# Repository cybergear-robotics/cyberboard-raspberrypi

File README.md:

# CyberBoard - Raspberry PI 4

This is the Kicad project for the CyberBoard Raspberry PI HAT. It has an ESP32S3 which is
connected via UART to the Raspberry PI. The microcontroller drives the cybergear 
motors via CAN. Furthermore a MOLEX CLIK connector is integrated in order
to communicate with the power distribution board [Holybro PM03D Pixhawk 5X Power
Module](https://docs.holybro.com/power-module-and-pdb/power-module/digital-power-module-pm-setup).

## Features

* 5V power supply connectior compatible with **Holybro PM03D Pixhawk** with
  support for the INA226 power monitor unit.
* ESP32S3 with dual-core CPU.
* CAN transceiver TJA1051T for communication with **Xiaomi CyberGears**.
* 5V fan connector for Raspberry PI with support for `gpio-fan` (PWM).
* Connector for external WS2812B LEDs.
* Connector 4x GPIO including 3.3V and 5V supply.
* Conenctor for lidar sensors from Slamtec (tested with RPLIDAR A3).
* 2x UART communication lines between ESP32S3 and Raspberry PI.
  * Serial log for debugging purposes, flashing and burning fuse-bits.
  * **ROS2 Serial Agent** communication
* **JTAG** connection between ESP32S3 and Raspberry PI
* Connector for external switch/button with LED support.

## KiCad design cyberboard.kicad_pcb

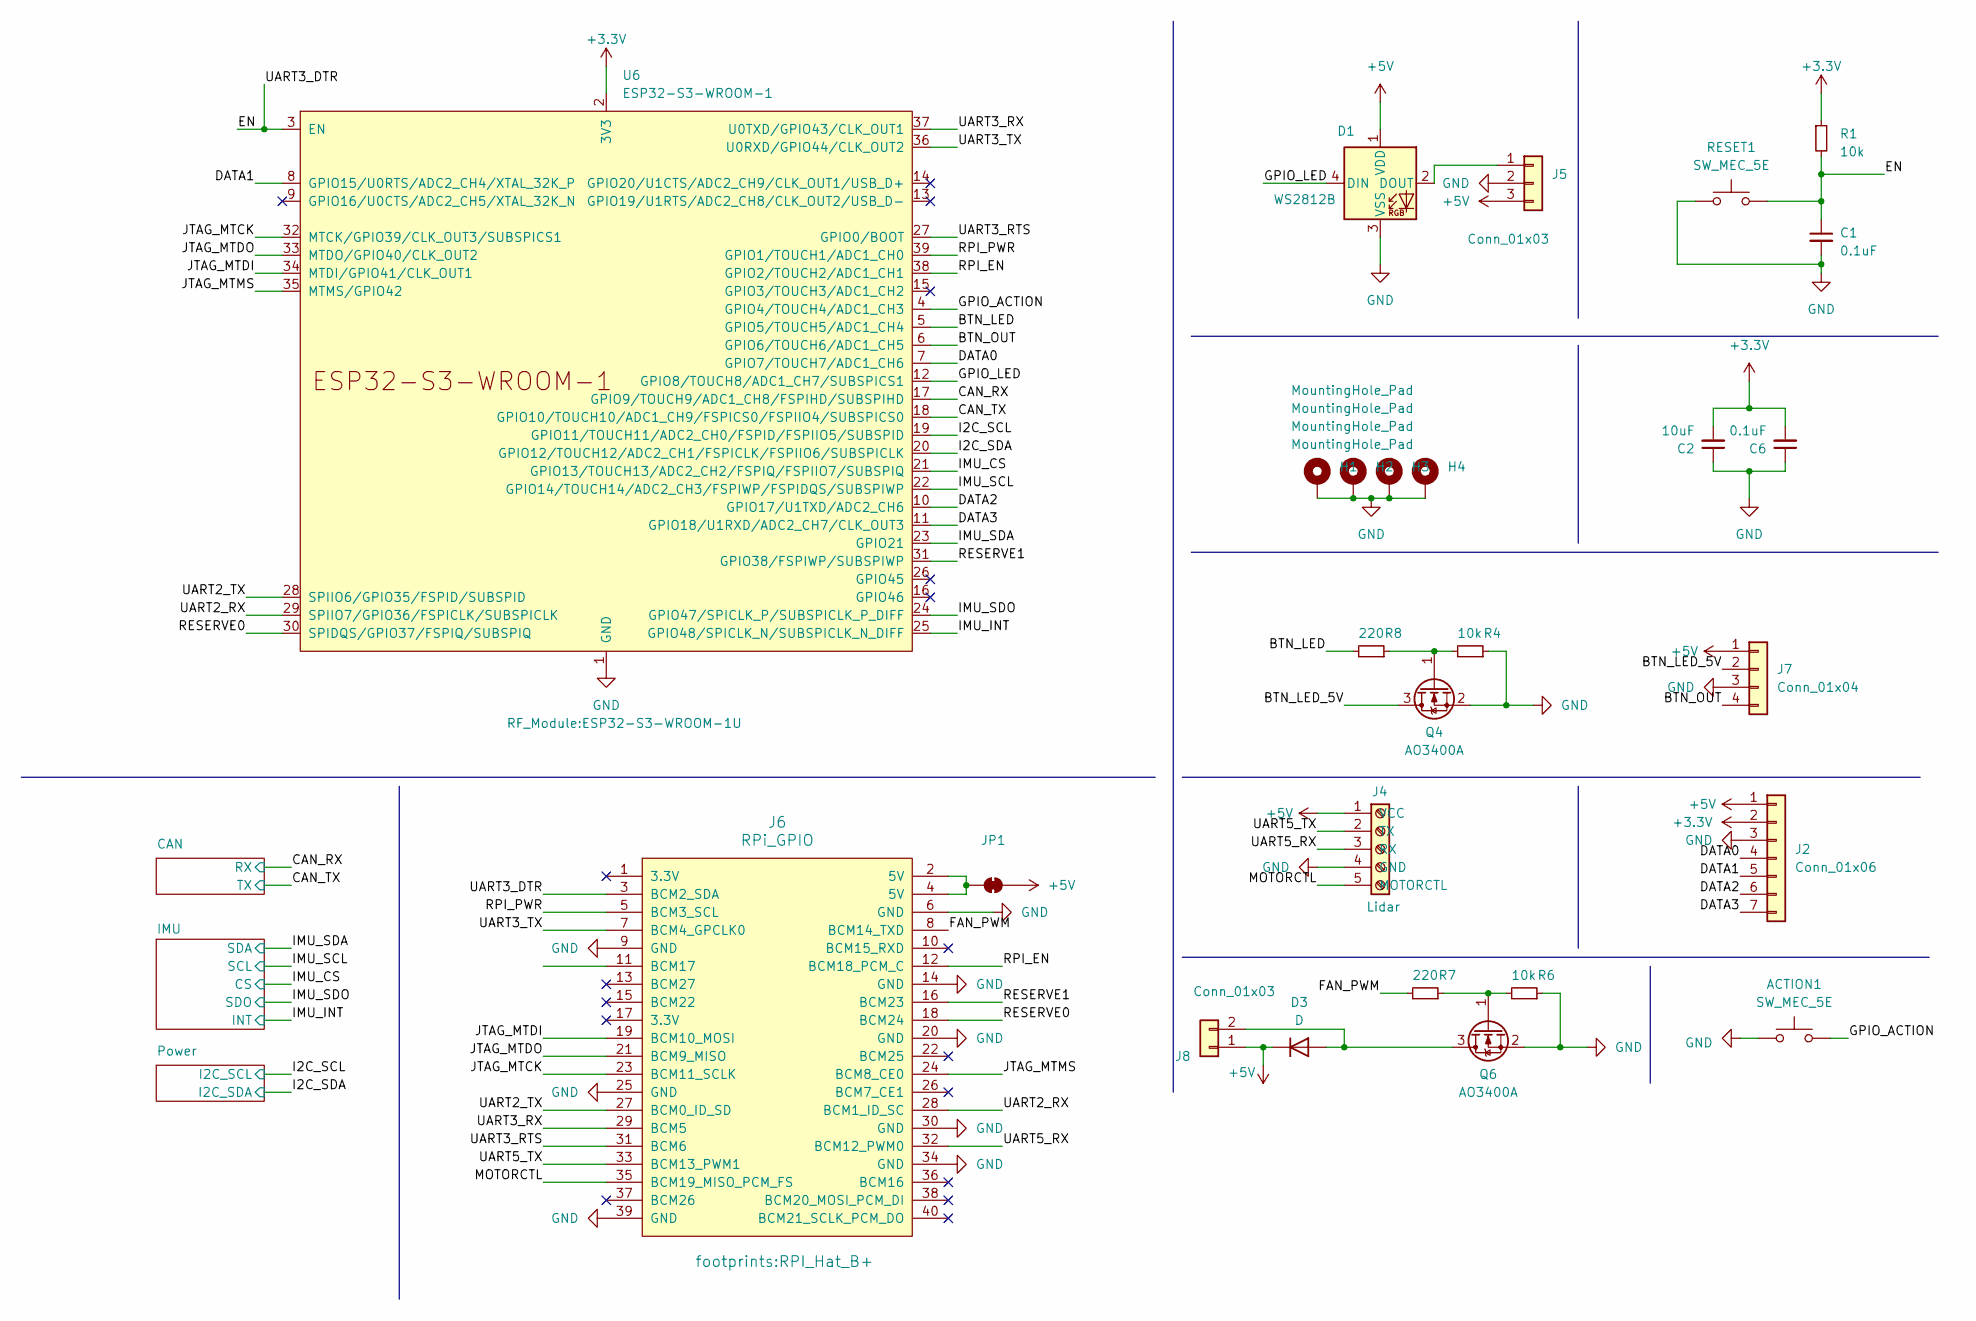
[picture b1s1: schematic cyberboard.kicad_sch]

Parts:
ACTION1: SW_MEC_5E; SW_PUSH_6mm_H5mm; LCSC C318884
C1, C6: 0.1uF; C_0805_2012Metric; LCSC C49678
C2: 10uF; C_0805_2012Metric; LCSC C15850
D1: WS2812B; LED_WS2812B_PLCC4_5.0x5.0mm_P3.2mm
D3: D; D_SOD-323; LCSC C191023
H1, H2, H3, H4: MountingHole_Pad; MountingHole_3.2mm_M3_DIN965_Pad
J2: Conn_01x06; JST_XH_B7B-XH-A_1x07_P2.50mm_Vertical
J4: Lidar; JST_XH_B5B-XH-A_1x05_P2.50mm_Vertical
J5: Conn_01x03; JST_XH_B3B-XH-A_1x03_P2.50mm_Vertical
J6: RPi_GPIO; RPI_Hat_B+
J7: Conn_01x04; JST_XH_B4B-XH-A_1x04_P2.50mm_Vertical
J8: Conn_01x03; JST_XH_B2B-XH-A_1x02_P2.50mm_Vertical
JP1: SolderJumper_2_Open; SolderJumper-2_P1.3mm_Bridged2Bar_RoundedPad1.0x1.5mm
Q4, Q6: AO3400A; SOT-23; LCSC C20917
R1, R4, R6: 10k; R_0805_2012Metric; LCSC C17414
R7, R8: 220; R_0805_2012Metric; LCSC C17557
RESET1: SW_MEC_5E; SW_PUSH_6mm_H5mm; LCSC C318884
U6: ESP32-S3-WROOM-1; ESP32-S3-WROOM-1U

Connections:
+3.3V: C2.2, C6.2, J2.2, R1.1, U6.2 (3V3); also elsewhere on the board
+5V: D1.1 (VDD), D3.1 (K), J2.1, J4.1 (VCC), J5.3, J7.1, J8.1, JP1.2 (B); also elsewhere on the board
/BTN_LED: R8.2, U6.5 (GPIO5/TOUCH5/ADC1_CH4)
/BTN_LED_5V: J7.2, Q4.3 (D)
/BTN_OUT: J7.4, U6.6 (GPIO6/TOUCH6/ADC1_CH5)
/CAN_RX: U6.17 (GPIO9/TOUCH9/ADC1_CH8/FSPIHD/SUBSPIHD); also elsewhere on the board
/CAN_TX: U6.18 (GPIO10/TOUCH10/ADC1_CH9/FSPICS0/FSPIIO4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); also elsewhere on the board
/DATA0: J2.4, U6.7 (GPIO7/TOUCH7/ADC1_CH6)
/DATA1: J2.5, U6.8 (GPIO15/U0RTS/ADC2_CH4/XTAL_32K_P)
/DATA2: J2.6, U6.10 (GPIO17/U1TXD/ADC2_CH6)
/DATA3: J2.7, U6.11 (GPIO18/U1RXD/ADC2_CH7/CLK_OUT3)
/EN: C1.1, J6.3 (BCM2_SDA), R1.2, RESET1.2, U6.3 (EN)
/FAN_PWM: J6.8 (BCM14_TXD), R7.2
/GPIO_ACTION: ACTION1.2, U6.4 (GPIO4/TOUCH4/ADC1_CH3)
/GPIO_LED: D1.4 (DIN), U6.12 (GPIO8/TOUCH8/ADC1_CH7/SUBSPICS1)
/I2C_SCL: U6.19 (GPIO11/TOUCH11/ADC2_CH0/FSPID/FSPIIO5/S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); also elsewhere on the board
/I2C_SDA: U6.20 (GPIO12/TOUCH12/ADC2_CH1/FSPICLK/FSPIIO6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); also elsewhere on the board
/IMU_CS: U6.21 (GPIO13/TOUCH13/ADC2_CH2/FSPIQ/FSPIIO7/S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); also elsewhere on the board
/IMU_INT: U6.25 (GPIO48/SPICLK_N/SUBSPICLK_N_DIFF); also elsewhere on the board
/IMU_SCL: U6.22 (GPIO14/TOUCH14/ADC2_CH3/FSPIWP/FSPIDQS/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); also elsewhere on the board
/IMU_SDA: U6.23 (GPIO21); also elsewhere on the board
/IMU_SDO: U6.24 (GPIO47/SPICLK_P/SUBSPICLK_P_DIFF); also elsewhere on the board
/JTAG_MTCK: J6.23 (BCM11_SCLK), U6.32 (MTCK/GPIO39/CLK_OUT3/SUBSPICS1)
/JTAG_MTDI: J6.19 (BCM10_MOSI), U6.34 (MTDI/GPIO41/CLK_OUT1)
/JTAG_MTDO: J6.21 (BCM9_MISO), U6.33 (MTDO/GPIO40/CLK_OUT2)
/JTAG_MTMS: J6.24 (BCM8_CE0), U6.35 (MTMS/GPIO42)
/MOTORCTL: J4.5 (MOTORCTL), J6.35 (BCM19_MISO_PCM_FS)
/RESERVE0: J6.18 (BCM24), U6.30 (SPIDQS/GPIO37/FSPIQ/SUBSPIQ)
/RESERVE1: J6.16 (BCM23), U6.31 (GPIO38/FSPIWP/SUBSPIWP)
/RPI_EN: J6.12 (BCM18_PCM_C), U6.38 (GPIO2/TOUCH2/ADC1_CH1)
/RPI_PWR: J6.5 (BCM3_SCL), U6.39 (GPIO1/TOUCH1/ADC1_CH0)
/UART2_RX: J6.28 (BCM1_ID_SC), U6.29 (SPIIO7/GPIO36/FSPICLK/SUBSPICLK)
/UART2_TX: J6.27 (BCM0_ID_SD), U6.28 (SPIIO6/GPIO35/FSPID/SUBSPID)
/UART3_RTS: J6.31 (BCM6), U6.27 (GPIO0/BOOT)
/UART3_RX: J6.29 (BCM5), U6.37 (U0TXD/GPIO43/CLK_OUT1)
/UART3_TX: J6.7 (BCM4_GPCLK0), U6.36 (U0RXD/GPIO44/CLK_OUT2)
/UART5_RX: J4.3 (RX), J6.32 (BCM12_PWM0)
/UART5_TX: J4.2 (TX), J6.33 (BCM13_PWM1)
GND: ACTION1.1, C1.2, C2.1, C6.1, D1.3 (VSS), H1.1, H2.1, H3.1, H4.1, J2.3, J4.4 (GND), J5.2, J6.6 (GND), J6.9 (GND), J6.14 (GND), J6.20 (GND), J6.25 (GND), J6.30 (GND), J6.34 (GND), J6.39 (GND), J7.3, Q4.2 (S), Q6.2 (S), R4.1, R6.1, RESET1.1, U6.1 (GND), U6.40 (GND), U6.41 (GND); also elsewhere on the board
unnamed: D1.2 (DOUT), J5.1
unnamed: D3.2 (A), J8.2, Q6.3 (D)
unnamed: J6.2 (5V), J6.4 (5V), JP1.1 (A)
unnamed: Q4.1 (G), R4.2, R8.1
unnamed: Q6.1 (G), R6.2, R7.1

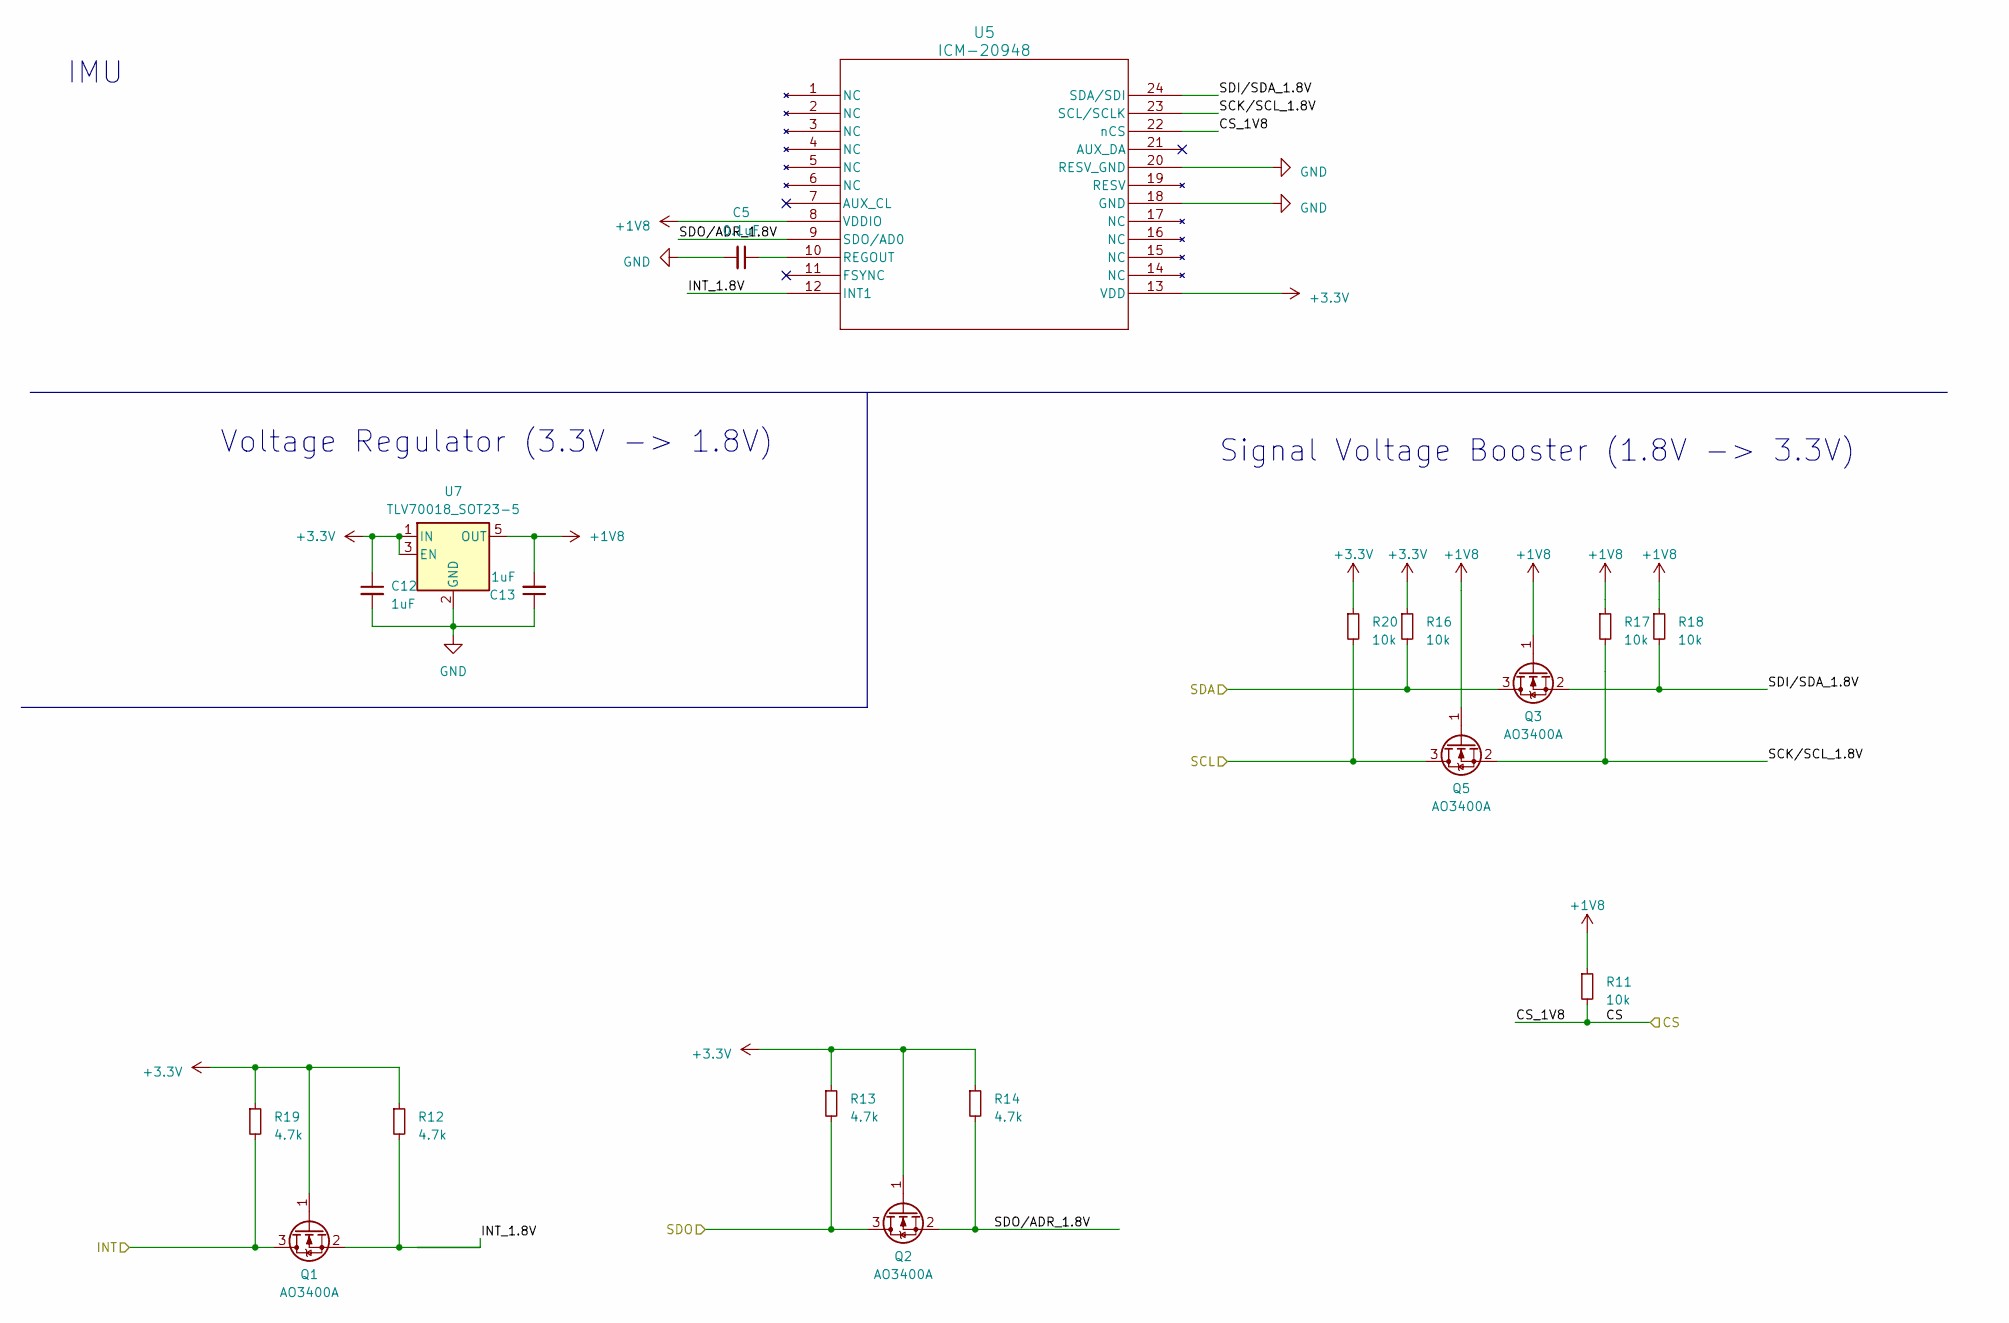
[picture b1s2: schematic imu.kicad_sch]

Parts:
C5: 0.1uF; C_0805_2012Metric; LCSC C49678
C12, C13: 1uF; C_0805_2012Metric; LCSC C28323
Q1, Q2, Q3, Q5: AO3400A; SOT-23; LCSC C20917
R11, R16, R17, R18, R20: 10k; R_0805_2012Metric; LCSC C17414
R12, R13, R14, R19: 4.7k; R_0805_2012Metric; LCSC C17673
U5: ICM-20948; QFN24_3X3X0P9_IVS; LCSC C726001
U7: TLV70018_SOT23-5; SOT-23-5; LCSC C79924

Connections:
+1V8: C13.2, Q3.1 (G), Q5.1 (G), R11.1, R17.1, R18.1, U5.8 (VDDIO), U7.5 (OUT)
+3.3V: C12.1, Q1.1 (G), Q2.1 (G), R12.1, R13.1, R14.1, R16.1, R19.1, R20.1, U5.13 (VDD), U7.1 (IN), U7.3 (EN); also elsewhere on the board
/IMU/INT_1.8V: Q1.2 (S), R12.2, U5.12 (INT1)
/IMU_CS: R11.2, U5.22 (nCS); also elsewhere on the board
/IMU_INT: Q1.3 (D), R19.2; also elsewhere on the board
/IMU_SCL: Q5.3 (D), R20.2; also elsewhere on the board
/IMU_SDA: Q3.3 (D), R16.2; also elsewhere on the board
/IMU_SDO: Q2.3 (D), R13.2; also elsewhere on the board
GND: C5.2, C12.2, C13.1, U5.18 (GND), U5.20 (RESV_GND), U7.2 (GND); also elsewhere on the board
unnamed: C5.1, U5.10 (REGOUT)

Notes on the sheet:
IMU
Signal Voltage Booster (1.8V -> 3.3V)
Voltage Regulator (3.3V -> 1.8V)

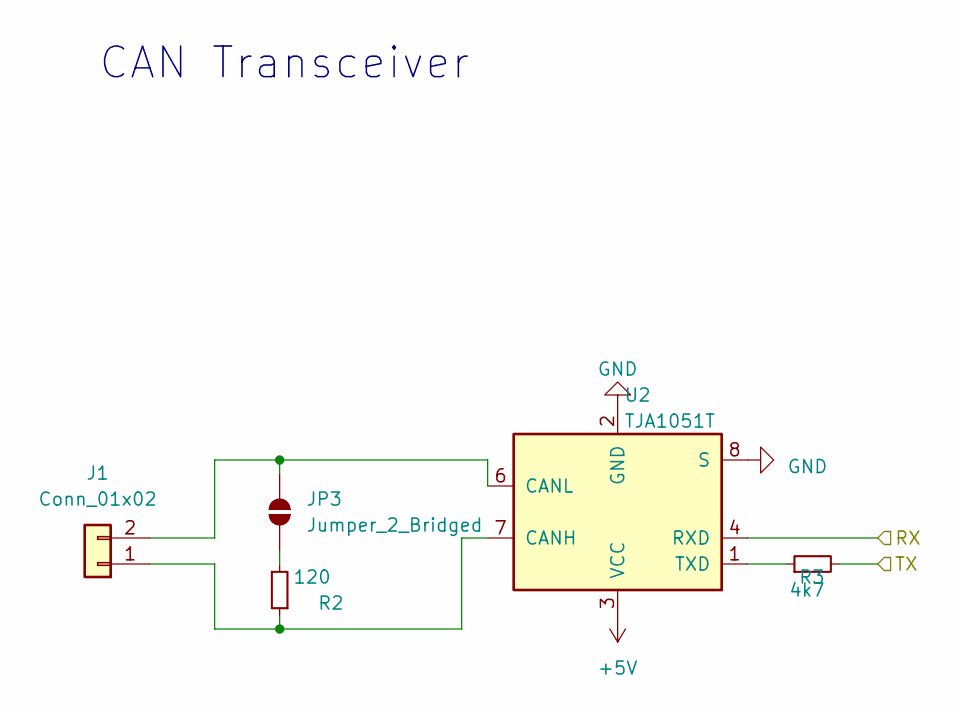
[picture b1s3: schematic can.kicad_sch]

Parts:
J1: Conn_01x02; JST_XH_B2B-XH-A_1x02_P2.50mm_Vertical
JP3: Jumper_2_Bridged; SolderJumper-2_P1.3mm_Open_RoundedPad1.0x1.5mm
R2: 120; R_0805_2012Metric; LCSC C17437
R3: 4k7; R_0805_2012Metric; LCSC C17673
U2: TJA1051T; SOIC-8_3.9x4.9mm_P1.27mm; LCSC C92211

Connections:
+5V: U2.3 (VCC); also elsewhere on the board
/CAN_RX: U2.4 (RXD); also elsewhere on the board
/CAN_TX: R3.2; also elsewhere on the board
GND: U2.2 (GND), U2.8 (S); also elsewhere on the board
unnamed: J1.1, R2.1, U2.7 (CANH)
unnamed: J1.2, JP3.2 (B), U2.6 (CANL)
unnamed: JP3.1 (A), R2.2
unnamed: R3.1, U2.1 (TXD)

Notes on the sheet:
CAN Transceiver

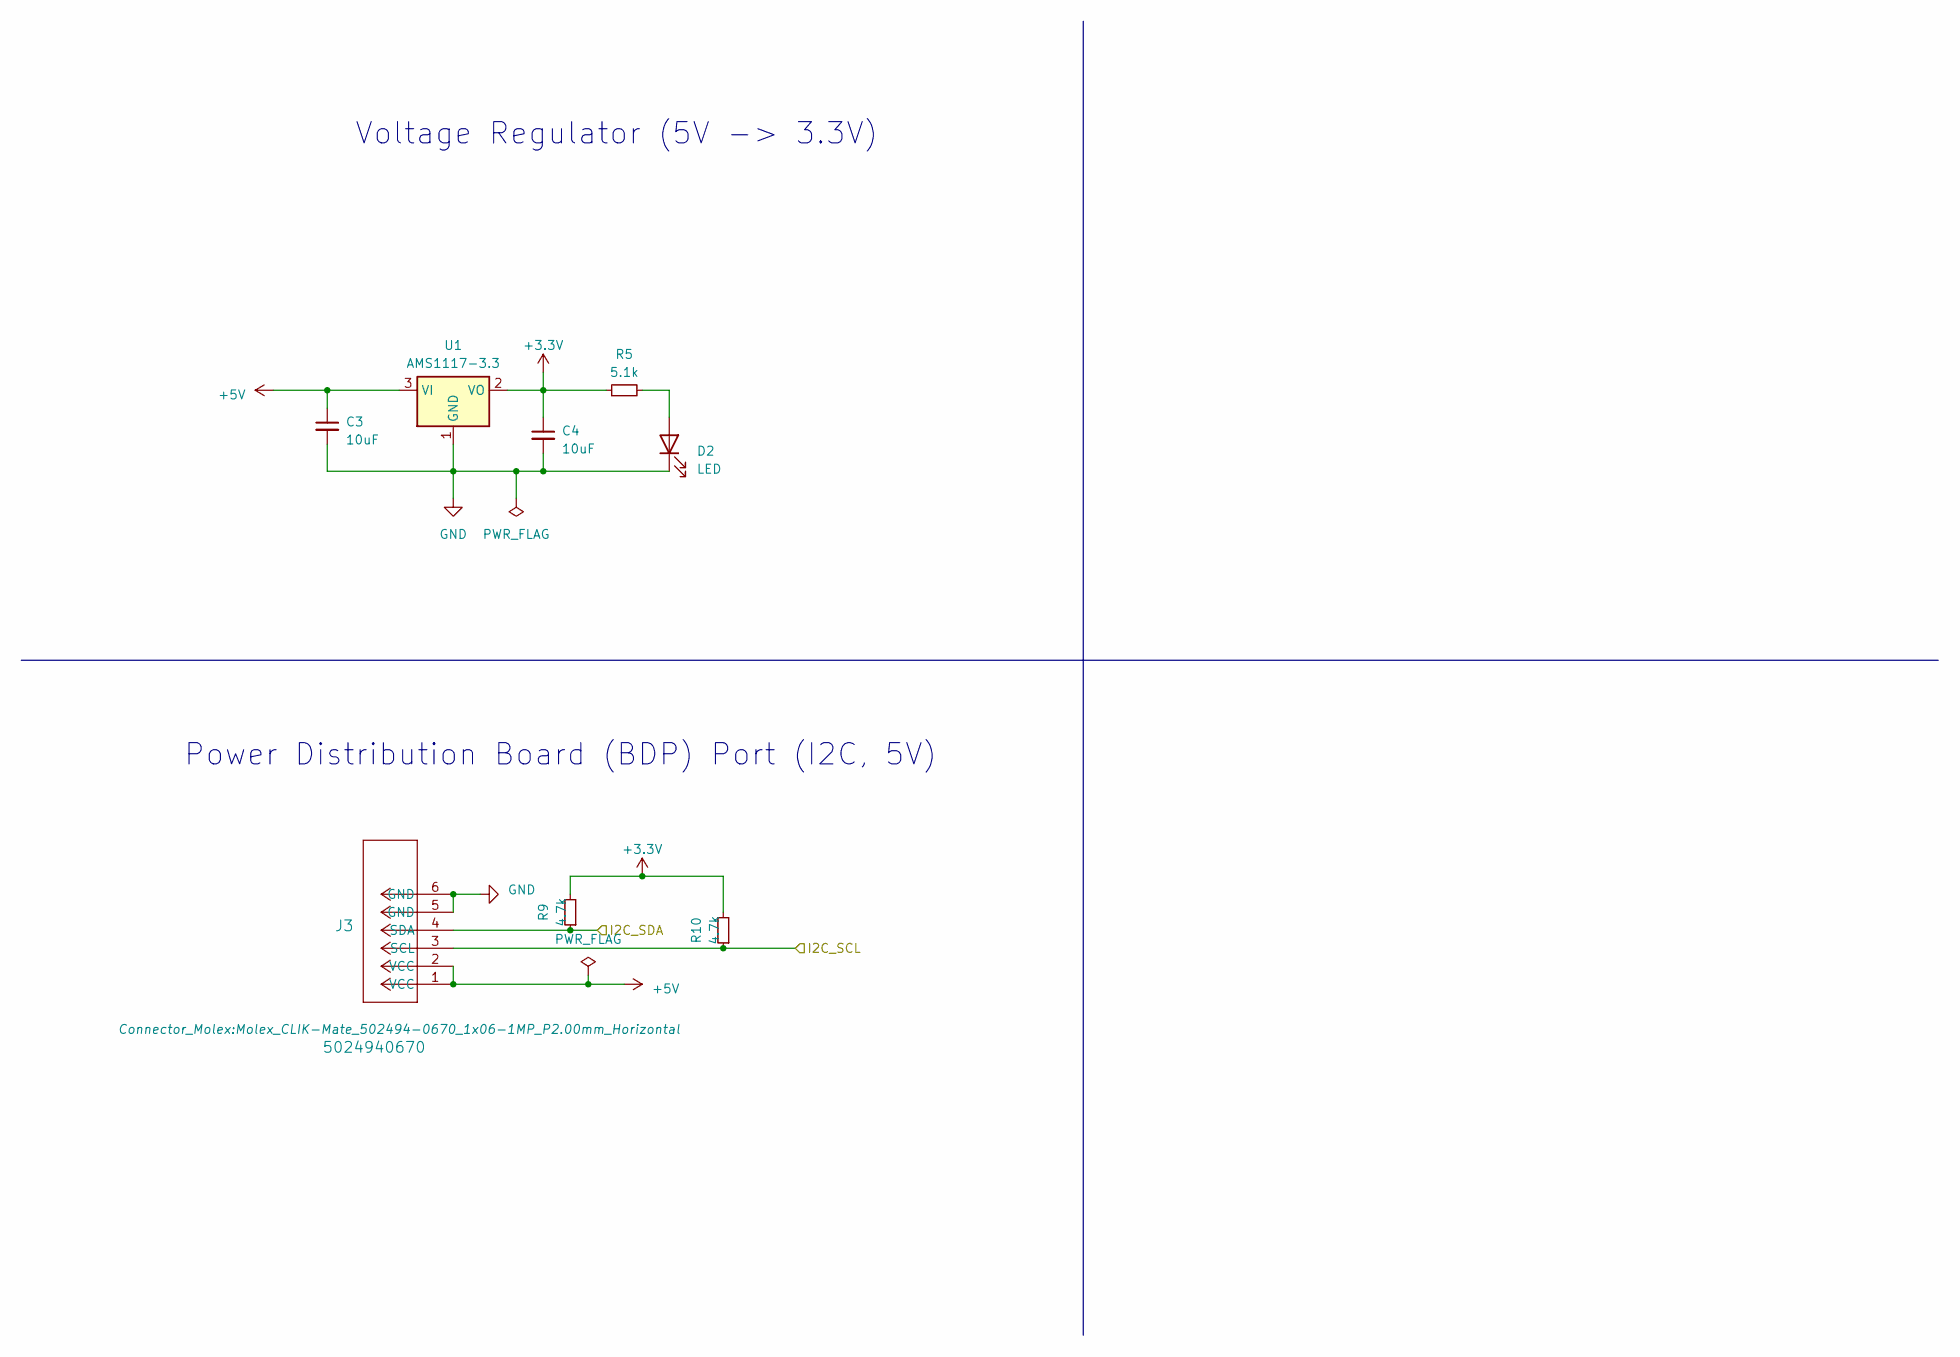
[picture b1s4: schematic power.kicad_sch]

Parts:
C3, C4: 10uF; C_0805_2012Metric; LCSC C15850
D2: LED; LED_0603_1608Metric; LCSC C2286
J3: 5024940670; Molex_CLIK-Mate_502494-0670_1x06-1MP_P2.00mm_Horizontal; LCSC C587930
R5: 5.1k; R_0805_2012Metric; LCSC C27834
R9, R10: 4.7k; R_0805_2012Metric; LCSC C17673
U1: AMS1117-3.3; SOT-223-3_TabPin2; LCSC C6186

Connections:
+3.3V: C4.1, R5.1, R9.2, R10.2, U1.2 (VO); also elsewhere on the board
+5V: C3.1, J3.1 (VCC), J3.2 (VCC), U1.3 (VI); also elsewhere on the board
/I2C_SCL: J3.3 (SCL), R10.1; also elsewhere on the board
/I2C_SDA: J3.4 (SDA), R9.1; also elsewhere on the board
GND: C3.2, C4.2, D2.1 (K), J3.5 (GND), J3.6 (GND), U1.1 (GND); also elsewhere on the board
unnamed: D2.2 (A), R5.2

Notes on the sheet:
Voltage Regulator (5V -> 3.3V)
Power Distribution Board (BDP) Port (I2C, 5V)

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
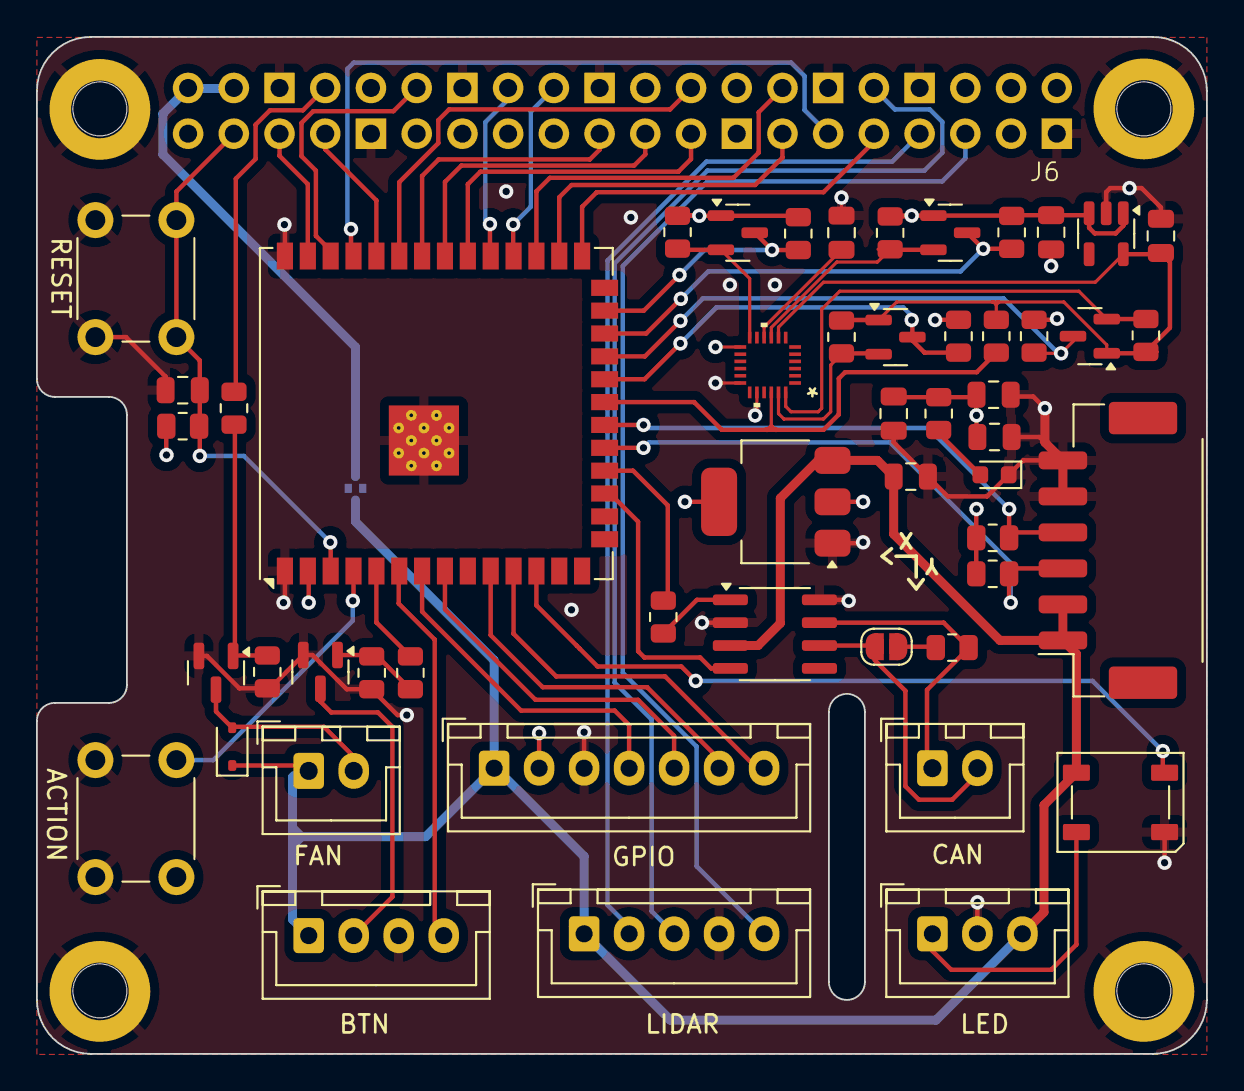
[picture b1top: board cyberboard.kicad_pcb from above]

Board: 4 copper layers, 65.0 x 56.5 mm, 57 parts (1 on the bottom side), 55 nets.

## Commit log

2025-02-19 inital commit with pcb for RPi
2025-03-15 fix bugs
2025-03-30 fix BTN mosfet connection
2025-03-30 swap CAN TX/RX
2025-03-30 swap CAN TX/RX at JST connector
2025-03-31 add LED connector and update FAN connector
2025-03-31 add missing part numbers for JLCPCB
2025-03-31 fix pcb layout
2025-03-31 add license and README
2025-03-31 update badge in README

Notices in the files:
README.md:
License: MIT
